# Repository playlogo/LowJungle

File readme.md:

# LowJungle

A low profile, ~65% keyboard, with:

- Hot swappable sockets
- Per key RGB backlight
- Wifi & BLE (but no battery)
- Integrated 3 port USB Hub

Links:

- [Onshape: Case](https://cad.onshape.com/documents/196ae99135554e28081e9cd8/w/09114671e2d692aadc408c6f/e/86be969bd7a114ceaf756b4a?renderMode=0&uiState=67d72bd2d4975832f10ffe5c)
- [Keyboard Layout Editor: Layout](https://www.keyboard-layout-editor.com/#/gists/81105ca4efea79bf3cdf03d682872e17)

## Firmware

For testing: KMK  
For production: QMK

> Circuitpython is soooo much nicer for finding errors in the hardware  
> Status KMK: Pins are correct, keymap is WIP

## PCB

- [Schematic](assets/schematic.pdf)
- No relevant ERC & DRC errors
- Size: 371.48mm x 133.35mm
- VCC for backlight LEDs can be controlled by the ESP32 using 2 mosfets
- Used libraries:
  - [Marbastlib, needs to be installed as plugin](https://github.com/ebastler/marbastlib/tree/main)
  - [easyeda2kicad, needs to be installed separately, used for downloading LCSC schematics & footprints](https://github.com/uPesy/easyeda2kicad.py)
    - Download `C2913204, C192893, C2891732, C778164, C2988369, C8547, C503996, C82942` using `easyeda2kicad --full --lcsc_id=<id>` (one-by-one, yes...)
  - `0_Custom`, included in the `libraries` folder, should load automatically

## Fabrication

> I'm print all parts myself using [the large scale 3D printer (Billig)](https://github.com/playlogo/billig) I'm build for [infill](https://github.com/hackclub/infill).

> Download the latest revision from [Onshape](https://cad.onshape.com/documents/196ae99135554e28081e9cd8/w/09114671e2d692aadc408c6f/e/86be969bd7a114ceaf756b4a?renderMode=0&uiState=67d72bd2d4975832f10ffe5c). STLs included with this repo are only meant as a backup if the onshape link ever stops working.

- Largest part: 380mmx145mm
- Recommended settings:
  - 6 wall loops
  - 6 solid top & bottom layers
  - 40% infill
- Notes:
  - `LowJungle-Backplate-V2.stl`: Should be solid
  - `LowJungle-Bumper-Bottom-V2.stl`: Print with TPU, 3x
  - `LowJungle-Bumper-Top-V2.stl`: 4x
  - `LowJungle-Frame-V2.stl`: Manually place tree supports for the USB connector cutouts

## BOM

**PCB:** [$36.34 at JLCPCB](assets/jlcpcb.png)

**Switches:** [Aliexpress: Gateron KS33 low-profile red, 90 for $38.63 => 0.43 per switch](https://de.aliexpress.com/item/1005007794069535.html)

**Keycaps:** [Aliexpress: Low profile set, 143 lily version, $21.61](https://de.aliexpress.com/item/1005004882406296.html)

**Stabilizers:** [Aliexpress: Gateron low-profile stabilizer set, 4x 2u 1x 6.25u, $13.79](https://de.aliexpress.com/item/1005005296240590.html)

**Fasteners:**

| Name | Price | Link |
|------|-------|------|
| 30x M2.5x3x3.5mm Heat insert | $1.83 | [Aliexpress](https://de.aliexpress.com/item/1005003582355741.html) |
| 14x M2.5x6mm Hex socket screw (for feet) | $1.41 | [Aliexpress](https://de.aliexpress.com/item/32810872544.html)|
| 16x M2.5x8mm Hex socket screw (for mounting frame) | $1.64 | [Aliexpress](https://de.aliexpress.com/item/32810872544.html) |
| 9x M3x10mm Hex socket screw | $1.79 | [Aliexpress](https://de.aliexpress.com/item/32810872544.html) |

Total: $6,67

**MCU:**

> Note: The ESP32S3 implementation is the same as in my [Hackpad](https://github.com/hackclub/hackpad/pull/570). Thus the cost can be drastically reduced when combining both LCSC orders:
>
> - -$3: Removed handling fee
> - -$6: Random shipping coupon
> - and often times the MOQ from hackpad also covers this project

|Name|Price|Link| Needed if combined order ? |
|----|-----|----|----------------------------|
|Espressif Systems ESP32-S3-WROOM-1-N8R2| $4.41| [LCSC](https://www.lcsc.com/product-detail/WiFi-Modules_Espressif-Systems-ESP32-S3-WROOM-1-N8R2_C2913204.html)| Yes|
| N-Channel mosfet | $0.6 for MOQ | [LCSC](https://www.lcsc.com/product-detail/MOSFETs_YONGYUTAI-SI2302_C2891732.html)| Yes |
|3.3V LDO | $0.48 for MOQ| [LCSC](https://www.lcsc.com/product-detail/Voltage-Regulators-Linear-Low-Drop-Out-LDO-Regulators_MICRONE-Nanjing-Micro-One-Elec-ME6211C33M5G-N_C82942.html?s_z=n_ME6211C33M5G-N)| No |
| USB-A female| $0.42 for MOQ | [LCSC](https://www.lcsc.com/product-detail/USB-Connectors_Shenzhen-Kinghelm-Elec-KH-AF90DIP-112_C503996.html?s_z=n_usb%20a)|No |
| USB-C female| $0.4 for MOQ | [LCSC](https://www.lcsc.com/product-detail/USB-Connectors_G-Switch-GT-USB-7010ASV_C2988369.html?s_z=n_G-Switch%20GT-USB-7010asv)|No |
| P-Channel mosfet | $0.49 for MOQ | [LCSC](https://www.lcsc.com/product-detail/MOSFETs_Jiangsu-Changjing-Electronics-Technology-Co-Ltd-CJ2301-S1_C8547.html)|No |
| Mini push button | $0.47 for MOQ | [LCSC](https://www.lcsc.com/product-detail/Tactile-Switches_G-Switch-GT-TC029A-H020-L1N_C778164.html?s_z=n_SKRKAEE020)|No |
| CoreChips SL2.1A USB Hub driver | $1.32 for MOQ | [LCSC](https://www.lcsc.com/product-detail/USB-HUB-Controllers_CoreChips-SL2-1A_C192893.html?s_z=n_C192893)|No |
|---|----|---|---|
| 1N4148 Diodes | $1.04 for 100 | [LCSC](https://www.lcsc.com/product-detail/Switching-Diodes_LangJie-1N4148_C18195411.html?s_z=n_1N4148%2520Diodes) | Yes |
|10uF 0805 Capacitor | $0.16 for MOQ| [LCSC](https://www.lcsc.com/product-detail/Multilayer-Ceramic-Capacitors-MLCC-SMD-SMT_Samsung-Electro-Mechanics-CL21A106KOQNNNE_C1713.html)| No|
| 100nF * | $0.3 for MOQ | [LCSC](https://www.lcsc.com/product-detail/Multilayer-Ceramic-Capacitors-MLCC-SMD-SMT_FH-Guangdong-Fenghua-Advanced-Tech-0805B104J500NT_C29926.html)|No|
| 1uF * | $1 for MOQ | [LCSC](https://www.lcsc.com/product-detail/Multilayer-Ceramic-Capacitors-MLCC-SMD-SMT_YAGEO-CC0805JKX7R9BB105_C541528.html) | No |
|10k 0805 Resistor | $0.13 for MOQ | [LCSC](https://www.lcsc.com/product-detail/Chip-Resistor-Surface-Mount_VO-SCR0805J10K_C5140188.html?s_z=n_resistor)| No|
| 5.1k * | $0.15 for MOQ | [LCSC](https://www.lcsc.com/product-detail/Chip-Resistor-Surface-Mount_UNI-ROYAL-Uniroyal-Elec-0805W8J0512T5E_C26023.html?s_z=n_resistor) | No |
| 100k * |  $0.13 for MOQ | [LCSC](https://www.lcsc.com/product-detail/Chip-Resistor-Surface-Mount_VO-SCR0805J100K_C3017875.html?s_z=n_resistor) | No |

Total (without combined order): $11.46  
Total (with combined order): $6.01

>Note: Combined LCSC order will be around ~$28 (including shipping) for both hackpad and hackboard

**Misc Electronics:**

|Name|Price|Link|
| ----- | ---- | ---- |
| SK6812 MINI-E | $2.85 for 100 | [Aliexpress](https://de.aliexpress.com/item/1005002782417198.html) |
| Gateron Low-profile hot-swap socket | $9.03 for 100 => $0.1 per socket | [Aliexpress](https://de.aliexpress.com/item/1005008078611488.html?spm=a2g0o.productlist.main.1.3d3470f0o9Li2s&algo_pvid=ef243bac-f923-4f5b-85e0-b6818cdc378c&pdp_ext_f=%7B%22order%22%3A%2223%22%2C%22eval%22%3A%221%22%7D&utparam-url=scene%3Asearch%7Cquery_from%3A) |
| Rotary-encoder | in stock | - |

Total: $11.88

**Other parts:**

|Name|Reason|Price|Link|
|----|------|-----|----|
| Poron foam, Bottom case <-> PCB, 2.5mm 15x35cm | Sound damping | $6.10 | [Aliexpress](https://de.aliexpress.com/item/1005007442653383.html)|
| EVA foam, PCB <-> Top plate , 1mm 35x50cm | Stability of top plate |  $2.05 | [Aliexpress](https://de.aliexpress.com/item/1005002856054113.html)|
|EVA foam, PCB <-> Keyswitch  | Sound damping | $3.42 | [Aliexpress](https://de.aliexpress.com/item/1005005556269716.html)|
|PE foam, Top plate <-> Keyswitch | Water spill protection (has happened before) | $2.19 | [Aliexpress](https://de.aliexpress.com/item/1005004804230184.html)|

Total: $13,76

### BOM total

**Fasteners:** $6,67
**PCB:** $36.34  
**Switches:** $38.63  
**Keycaps:** $21.61  
**Stabilizers:** $13.79  
**MCU:** $6.01  
**Misc Electronics:** $11.88  
**Other parts:** $13,76

**Total:** $148,69

> Note: Aliexpress prices are only valid until 26. March (15. anniversary sale)
> => If the grant is issued after 24. March, it would be awesome to have ~$15 buffer for changed prices. The unused amount would be returned to HackClub.

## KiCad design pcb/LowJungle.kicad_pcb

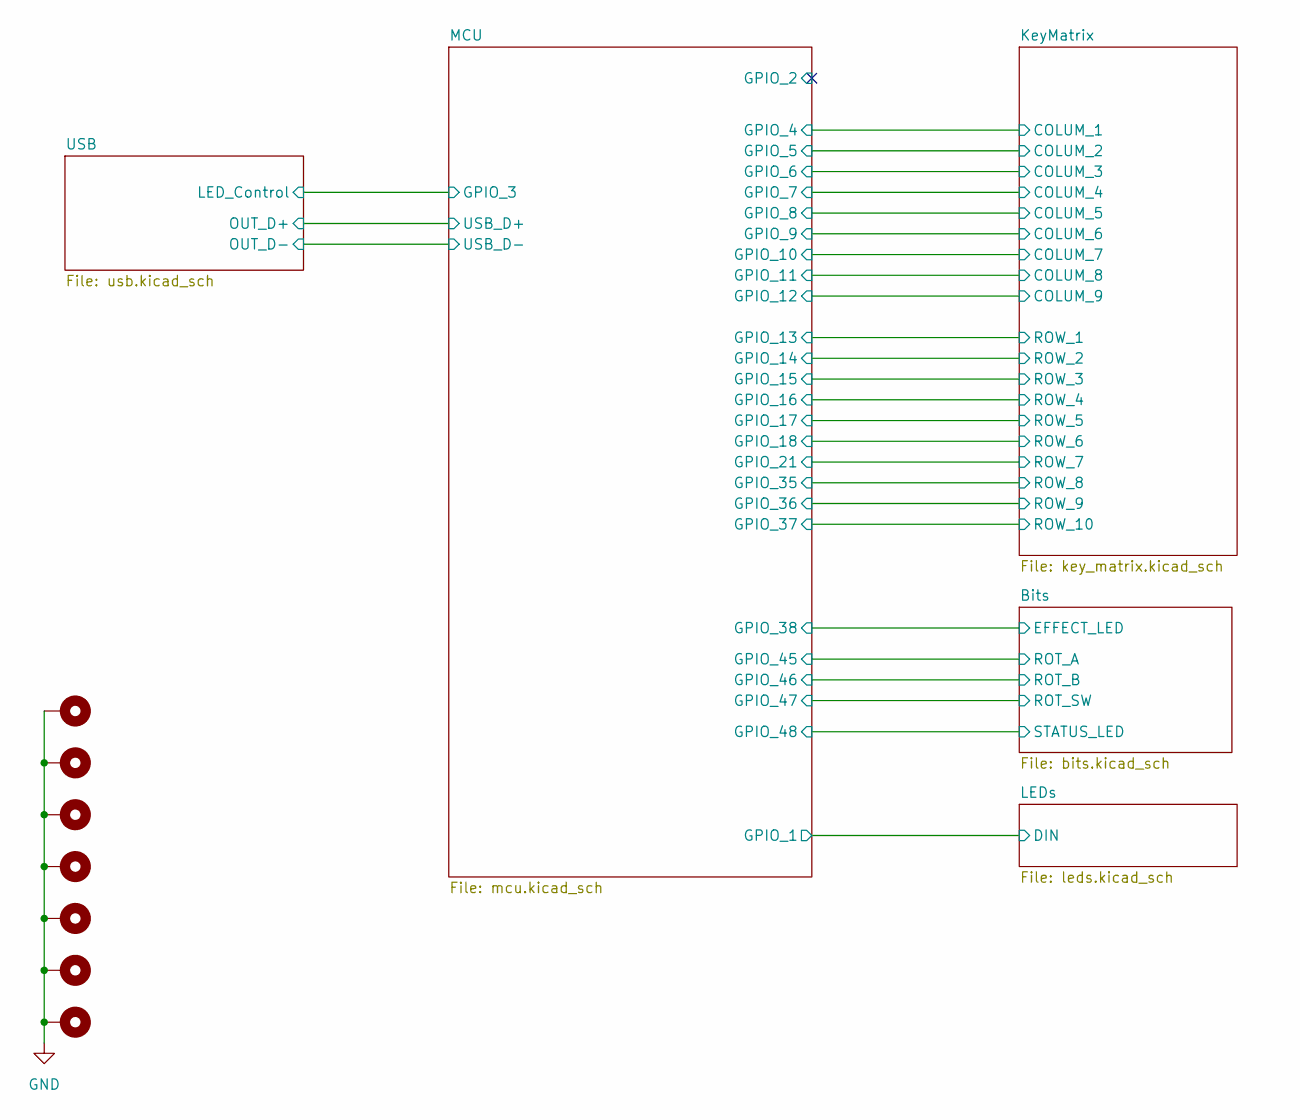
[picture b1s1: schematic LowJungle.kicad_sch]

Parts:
H1, H2, H3, H4, H5, H6, H7: MountingHole_Pad; MountingHole_3.2mm_M3_DIN965_Pad_TopOnly

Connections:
GND: H1.1, H2.1, H3.1, H4.1, H5.1, H6.1, H7.1; also elsewhere on the board

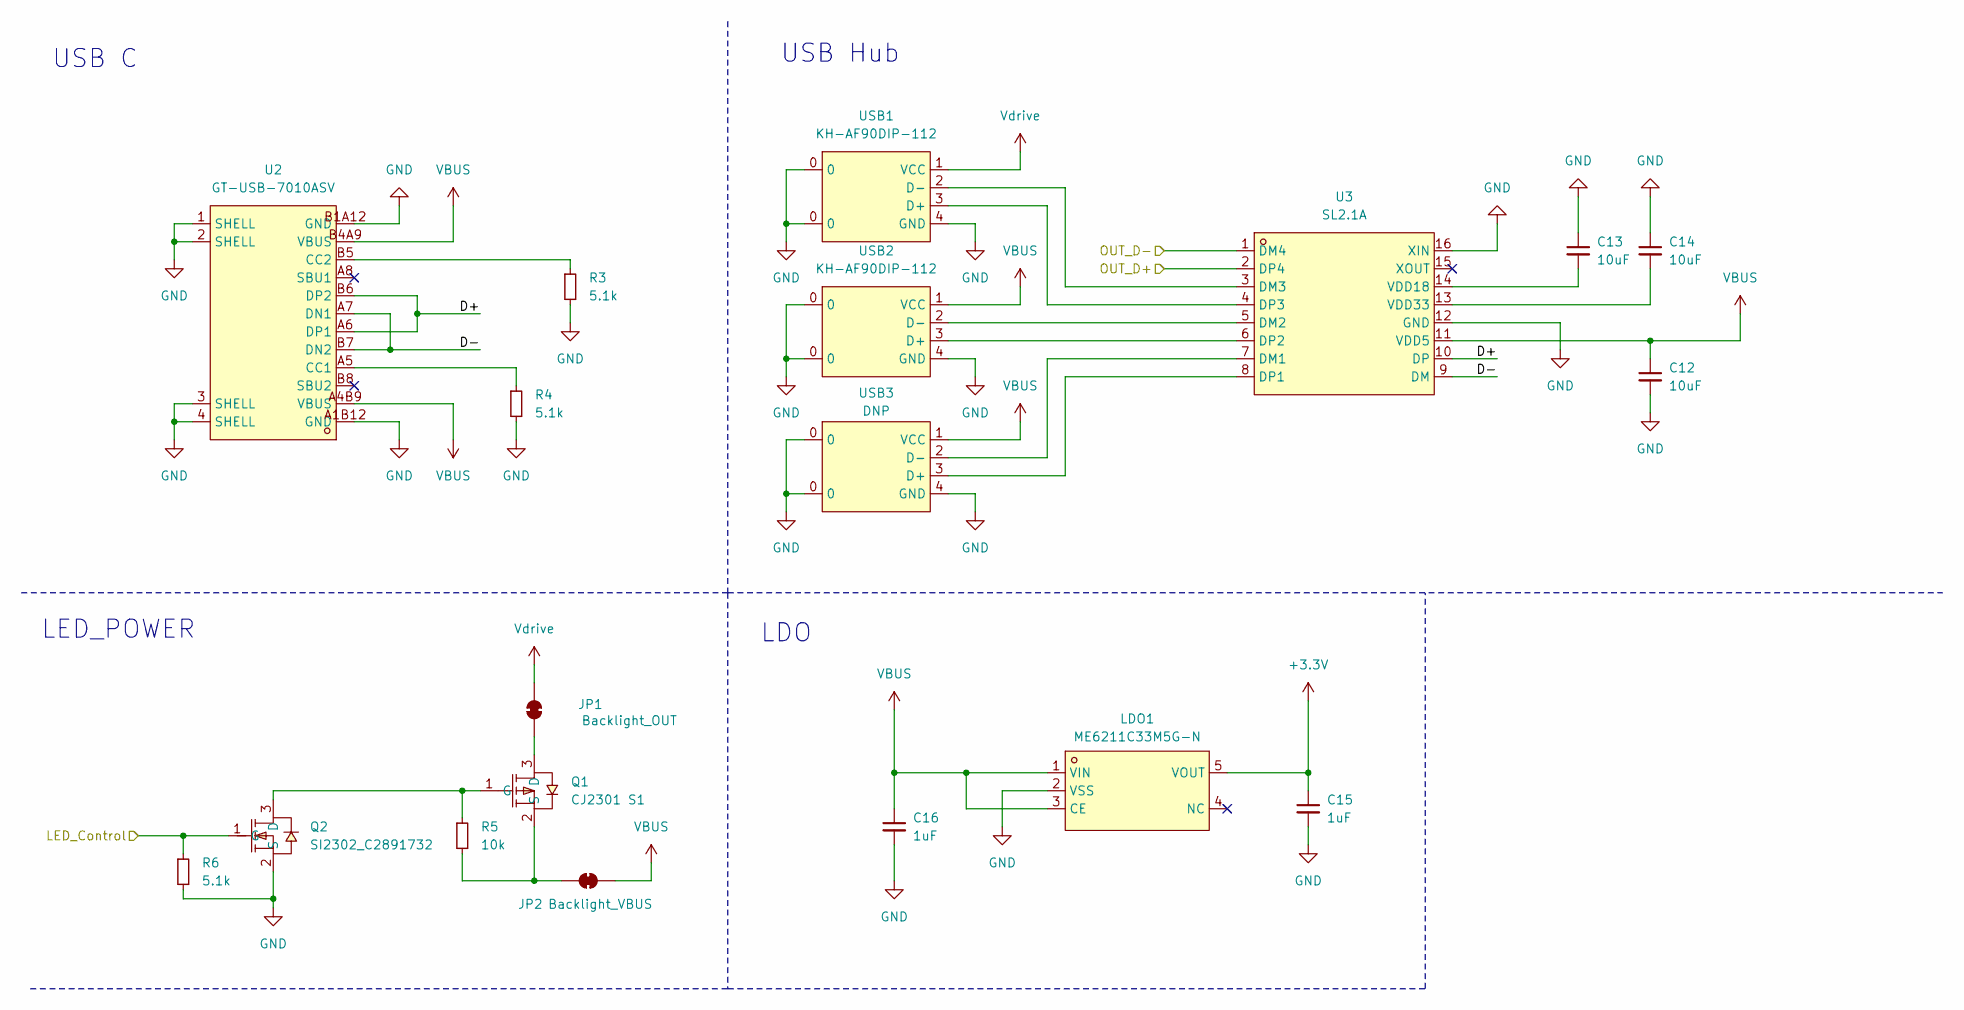
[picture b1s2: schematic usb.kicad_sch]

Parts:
C12, C13, C14: 10uF; C_0805_2012Metric_Pad1.18x1.45mm_HandSolder
C15, C16: 1uF; C_0805_2012Metric_Pad1.18x1.45mm_HandSolder
JP1: Backlight_OUT; SolderJumper-2_P1.3mm_Bridged2Bar_RoundedPad1.0x1.5mm
JP2: Backlight_VBUS; SolderJumper-2_P1.3mm_Bridged2Bar_RoundedPad1.0x1.5mm
LDO1: ME6211C33M5G-N; SOT-23-5_L3.0-W1.7-P0.95-LS2.8-BL; LCSC Part C82942
Q1: CJ2301 S1; SOT-23-3_L3.0-W1.7-P0.95-LS2.9-BR; LCSC Part C8547
Q2: SI2302_C2891732; SOT-23-3_L2.9-W1.3-P1.90-LS2.4-BR; LCSC Part C2891732
R3, R4, R6: 5.1k; R_0805_2012Metric_Pad1.20x1.40mm_HandSolder
R5: 10k; R_0805_2012Metric_Pad1.20x1.40mm_HandSolder
U2: GT-USB-7010ASV; USB-C-SMD_G-SWITCH_GT-USB-7010ASV; LCSC Part C2988369
U3: SL2.1A; SOP-16_L10.0-W3.9-P1.27-LS6.0-BL; LCSC Part C192893
USB1, USB2: KH-AF90DIP-112; USB-A-TH_USB-A-F-90; LCSC Part C503996
USB3: DNP; USB-A-TH_USB-A-F-90; LCSC Part C503996

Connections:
+3.3V: C15.1, LDO1.5 (VOUT); also elsewhere on the board
/MCU/GPIO_3: Q2.1 (G), R6.1; also elsewhere on the board
/MCU/USB_D+: U3.2 (DP4); also elsewhere on the board
/MCU/USB_D-: U3.1 (DM4); also elsewhere on the board
/USB/D+: U2.A6 (DP1), U2.B6 (DP2), U3.10 (DP)
/USB/D-: U2.A7 (DN1), U2.B7 (DN2), U3.9 (DM)
GND: C12.2, C13.1, C14.1, C15.2, C16.2, LDO1.2 (VSS), Q2.2 (S), R3.2, R4.2, R6.2, U2.1 (SHELL), U2.2 (SHELL), U2.3 (SHELL), U2.4 (SHELL), U2.A1B12 (GND), U2.B1A12 (GND), U3.12 (GND), U3.16 (XIN), USB1.0, USB1.4 (GND), USB2.0, USB2.4 (GND), USB3.0, USB3.4 (GND); also elsewhere on the board
unnamed: JP1.1 (A), Q1.3 (D)
unnamed: JP2.1 (A), Q1.2 (S), R5.2
unnamed: Q1.1 (G), Q2.3 (D), R5.1
unnamed: R4.1, U2.A5 (CC1)
unnamed: R3.1, U2.B5 (CC2)
unnamed: U3.7 (DM1), USB3.2 (D-)
unnamed: U3.5 (DM2), USB2.2 (D-)
unnamed: U3.3 (DM3), USB1.2 (D-)
unnamed: U3.8 (DP1), USB3.3 (D+)
unnamed: U3.6 (DP2), USB2.3 (D+)
unnamed: U3.4 (DP3), USB1.3 (D+)
unnamed: C13.2, U3.14 (VDD18)
unnamed: C14.2, U3.13 (VDD33)
VBUS: C12.1, C16.1, JP2.2 (B), LDO1.1 (VIN), LDO1.3 (CE), U2.A4B9 (VBUS), U2.B4A9 (VBUS), U3.11 (VDD5), USB2.1 (VCC), USB3.1 (VCC); also elsewhere on the board
Vdrive: JP1.2 (B), USB1.1 (VCC); also elsewhere on the board

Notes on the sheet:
USB Hub
LED_POWER
USB C
LDO

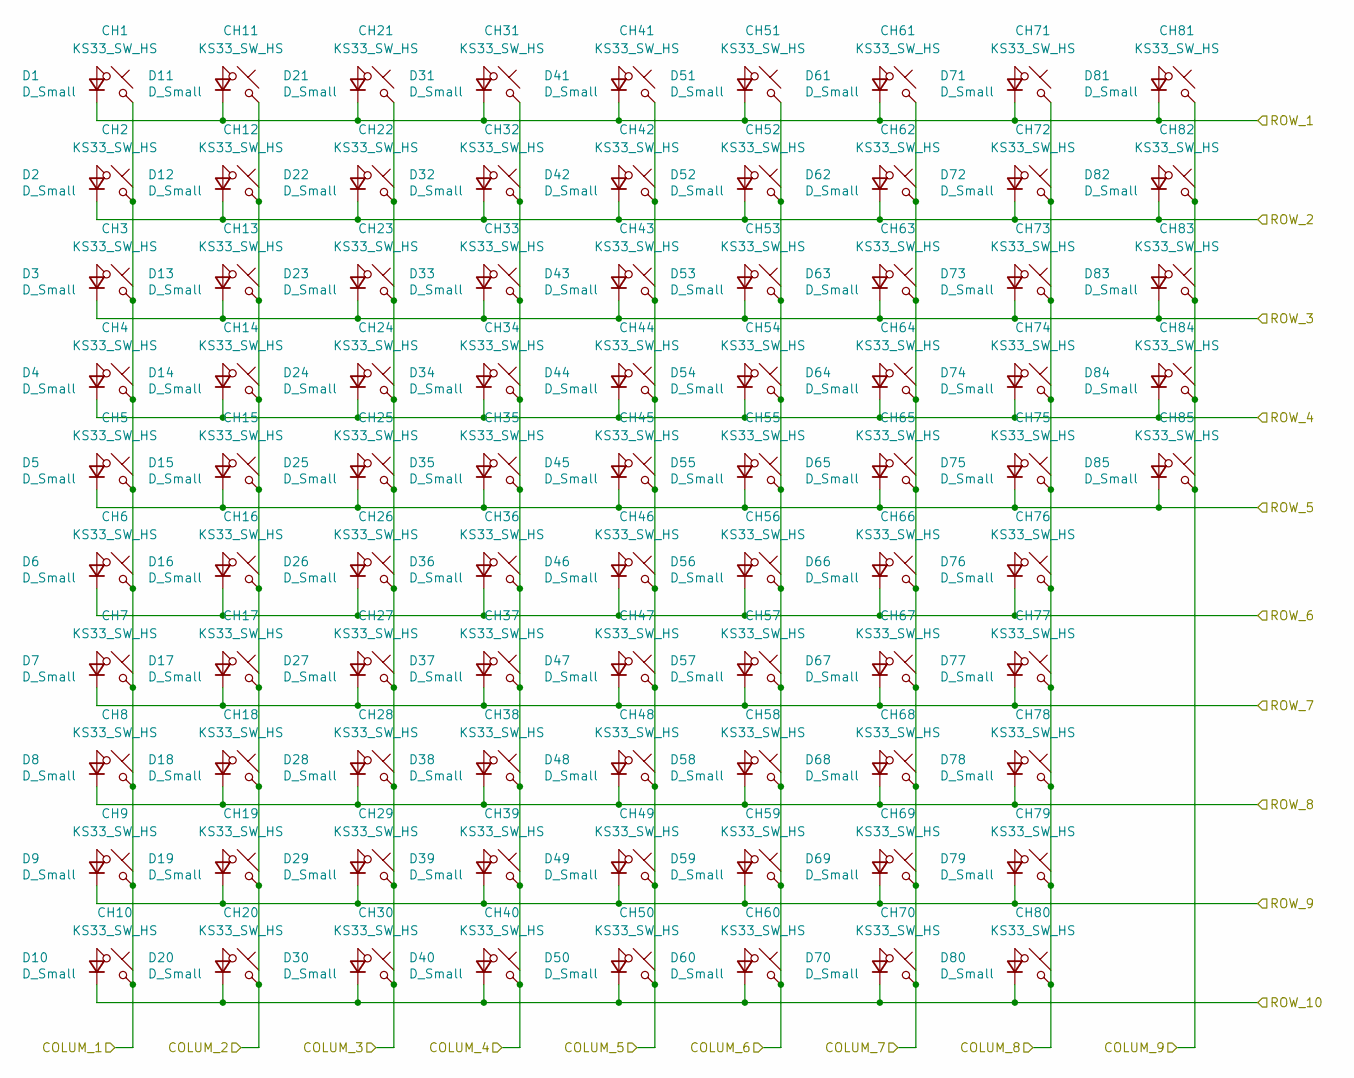
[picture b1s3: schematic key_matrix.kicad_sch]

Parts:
CH1, CH2, CH7, CH8, CH9, CH10, CH12, CH13, CH14, CH15, CH16, CH18, CH19, CH20, CH21, CH22, CH23, CH24, CH25, CH26, CH27, CH28, CH29, CH30, CH31, CH32, CH33, CH34, CH35, CH36, CH37, CH38, CH39, CH40, CH41, CH42, CH43, CH44, CH45, CH46, CH47, CH48, CH49, CH50, CH51, CH52, CH53, CH54, CH55, CH56, CH57, CH58, CH59, CH60, CH61, CH62, CH63, CH64, CH65, CH67, CH70, CH74, CH75, CH76, CH77, CH78, CH79, CH80, CH81, CH82, CH83, CH84, CH85: KS33_SW_HS; SW_KS33_HS_KS-2P02B01-02_HS_1u
CH3, CH68: KS33_SW_HS; SW_KS33_HS_KS-2P02B01-02_1.5u
CH4: KS33_SW_HS; SW_KS33_HS_KS-2P02B01-02_1.75u
CH5, CH6, CH11, CH17, CH66, CH69, CH71, CH72, CH73: KS33_SW_HS; SW_KS33_HS_KS-2P02B01-02_1.25u
D1, D2, D3, D4, D5, D6, D7, D8, D9, D10, D11, D12, D13, D14, D15, D16, D17, D18, D19, D20, D21, D22, D23, D24, D25, D26, D27, D28, D29, D30, D31, D32, D33, D34, D35, D36, D37, D38, D39, D40, D41, D42, D43, D44, D45, D46, D47, D48, D49, D50, D51, D52, D53, D54, D55, D56, D57, D58, D59, D60, D61, D62, D63, D64, D65, D66, D67, D68, D69, D70, D71, D72, D73, D74, D75, D76, D77, D78, D79, D80, D81, D82, D83, D84, D85: D_Small; D_DO-35_SOD27_P7.62mm_Horizontal

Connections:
/KeyMatrix/COLUM_1: CH1.2, CH2.2, CH3.2, CH4.2, CH5.2, CH6.2, CH7.2, CH8.2, CH9.2, CH10.2; also elsewhere on the board
/KeyMatrix/COLUM_2: CH11.2, CH12.2, CH13.2, CH14.2, CH15.2, CH16.2, CH17.2, CH18.2, CH19.2, CH20.2; also elsewhere on the board
/KeyMatrix/COLUM_3: CH21.2, CH22.2, CH23.2, CH24.2, CH25.2, CH26.2, CH27.2, CH28.2, CH29.2, CH30.2; also elsewhere on the board
/KeyMatrix/COLUM_4: CH31.2, CH32.2, CH33.2, CH34.2, CH35.2, CH36.2, CH37.2, CH38.2, CH39.2, CH40.2; also elsewhere on the board
/KeyMatrix/COLUM_5: CH41.2, CH42.2, CH43.2, CH44.2, CH45.2, CH46.2, CH47.2, CH48.2, CH49.2, CH50.2; also elsewhere on the board
/KeyMatrix/COLUM_6: CH51.2, CH52.2, CH53.2, CH54.2, CH55.2, CH56.2, CH57.2, CH58.2, CH59.2, CH60.2; also elsewhere on the board
/KeyMatrix/COLUM_7: CH61.2, CH62.2, CH63.2, CH64.2, CH65.2, CH66.2, CH67.2, CH68.2, CH69.2, CH70.2; also elsewhere on the board
/KeyMatrix/COLUM_8: CH71.2, CH72.2, CH73.2, CH74.2, CH75.2, CH76.2, CH77.2, CH78.2, CH79.2, CH80.2; also elsewhere on the board
/KeyMatrix/COLUM_9: CH81.2, CH82.2, CH83.2, CH84.2, CH85.2; also elsewhere on the board
/KeyMatrix/ROW_1: D1.1 (K), D11.1 (K), D21.1 (K), D31.1 (K), D41.1 (K), D51.1 (K), D61.1 (K), D71.1 (K), D81.1 (K); also elsewhere on the board
/KeyMatrix/ROW_2: D2.1 (K), D12.1 (K), D22.1 (K), D32.1 (K), D42.1 (K), D52.1 (K), D62.1 (K), D72.1 (K), D82.1 (K); also elsewhere on the board
/KeyMatrix/ROW_3: D3.1 (K), D13.1 (K), D23.1 (K), D33.1 (K), D43.1 (K), D53.1 (K), D63.1 (K), D73.1 (K), D83.1 (K); also elsewhere on the board
/KeyMatrix/ROW_4: D4.1 (K), D14.1 (K), D24.1 (K), D34.1 (K), D44.1 (K), D54.1 (K), D64.1 (K), D74.1 (K), D84.1 (K); also elsewhere on the board
/KeyMatrix/ROW_5: D5.1 (K), D15.1 (K), D25.1 (K), D35.1 (K), D45.1 (K), D55.1 (K), D65.1 (K), D75.1 (K), D85.1 (K); also elsewhere on the board
/KeyMatrix/ROW_6: D6.1 (K), D16.1 (K), D26.1 (K), D36.1 (K), D46.1 (K), D56.1 (K), D66.1 (K), D76.1 (K); also elsewhere on the board
/KeyMatrix/ROW_7: D7.1 (K), D17.1 (K), D27.1 (K), D37.1 (K), D47.1 (K), D57.1 (K), D67.1 (K), D77.1 (K); also elsewhere on the board
/KeyMatrix/ROW_8: D8.1 (K), D18.1 (K), D28.1 (K), D38.1 (K), D48.1 (K), D58.1 (K), D68.1 (K), D78.1 (K); also elsewhere on the board
/KeyMatrix/ROW_9: D9.1 (K), D19.1 (K), D29.1 (K), D39.1 (K), D49.1 (K), D59.1 (K), D69.1 (K), D79.1 (K); also elsewhere on the board
/KeyMatrix/ROW_10: D10.1 (K), D20.1 (K), D30.1 (K), D40.1 (K), D50.1 (K), D60.1 (K), D70.1 (K), D80.1 (K); also elsewhere on the board
unnamed: CH1.1, D1.2 (A)
unnamed: CH2.1, D2.2 (A)
unnamed: CH3.1, D3.2 (A)
unnamed: CH4.1, D4.2 (A)
unnamed: CH5.1, D5.2 (A)
unnamed: CH6.1, D6.2 (A)
unnamed: CH7.1, D7.2 (A)
unnamed: CH8.1, D8.2 (A)
unnamed: CH9.1, D9.2 (A)
unnamed: CH10.1, D10.2 (A)
unnamed: CH11.1, D11.2 (A)
unnamed: CH12.1, D12.2 (A)
unnamed: CH13.1, D13.2 (A)
unnamed: CH14.1, D14.2 (A)
unnamed: CH15.1, D15.2 (A)
unnamed: CH16.1, D16.2 (A)
unnamed: CH17.1, D17.2 (A)
unnamed: CH18.1, D18.2 (A)
unnamed: CH19.1, D19.2 (A)
unnamed: CH20.1, D20.2 (A)
unnamed: CH21.1, D21.2 (A)
unnamed: CH22.1, D22.2 (A)
unnamed: CH23.1, D23.2 (A)
unnamed: CH24.1, D24.2 (A)
unnamed: CH25.1, D25.2 (A)
unnamed: CH26.1, D26.2 (A)
unnamed: CH27.1, D27.2 (A)
unnamed: CH28.1, D28.2 (A)
unnamed: CH29.1, D29.2 (A)
unnamed: CH30.1, D30.2 (A)
unnamed: CH31.1, D31.2 (A)
unnamed: CH32.1, D32.2 (A)
unnamed: CH33.1, D33.2 (A)
unnamed: CH34.1, D34.2 (A)
unnamed: CH35.1, D35.2 (A)
unnamed: CH36.1, D36.2 (A)
unnamed: CH37.1, D37.2 (A)
unnamed: CH38.1, D38.2 (A)
unnamed: CH39.1, D39.2 (A)
unnamed: CH40.1, D40.2 (A)
unnamed: CH41.1, D41.2 (A)
unnamed: CH42.1, D42.2 (A)
unnamed: CH43.1, D43.2 (A)
unnamed: CH44.1, D44.2 (A)
unnamed: CH45.1, D45.2 (A)
unnamed: CH46.1, D46.2 (A)
unnamed: CH47.1, D47.2 (A)
unnamed: CH48.1, D48.2 (A)
unnamed: CH49.1, D49.2 (A)
unnamed: CH50.1, D50.2 (A)
unnamed: CH51.1, D51.2 (A)
unnamed: CH52.1, D52.2 (A)
unnamed: CH53.1, D53.2 (A)
unnamed: CH54.1, D54.2 (A)
unnamed: CH55.1, D55.2 (A)
unnamed: CH56.1, D56.2 (A)
unnamed: CH57.1, D57.2 (A)
unnamed: CH58.1, D58.2 (A)
unnamed: CH59.1, D59.2 (A)
unnamed: CH60.1, D60.2 (A)
unnamed: CH61.1, D61.2 (A)
unnamed: CH62.1, D62.2 (A)
unnamed: CH63.1, D63.2 (A)
unnamed: CH64.1, D64.2 (A)
unnamed: CH65.1, D65.2 (A)
unnamed: CH66.1, D66.2 (A)
unnamed: CH67.1, D67.2 (A)
unnamed: CH68.1, D68.2 (A)
unnamed: CH69.1, D69.2 (A)
unnamed: CH70.1, D70.2 (A)
unnamed: CH71.1, D71.2 (A)
unnamed: CH72.1, D72.2 (A)
unnamed: CH73.1, D73.2 (A)
unnamed: CH74.1, D74.2 (A)
unnamed: CH75.1, D75.2 (A)
unnamed: CH76.1, D76.2 (A)
unnamed: CH77.1, D77.2 (A)
unnamed: CH78.1, D78.2 (A)
unnamed: CH79.1, D79.2 (A)
unnamed: CH80.1, D80.2 (A)
unnamed: CH81.1, D81.2 (A)
unnamed: CH82.1, D82.2 (A)
unnamed: CH83.1, D83.2 (A)
unnamed: CH84.1, D84.2 (A)
unnamed: CH85.1, D85.2 (A)

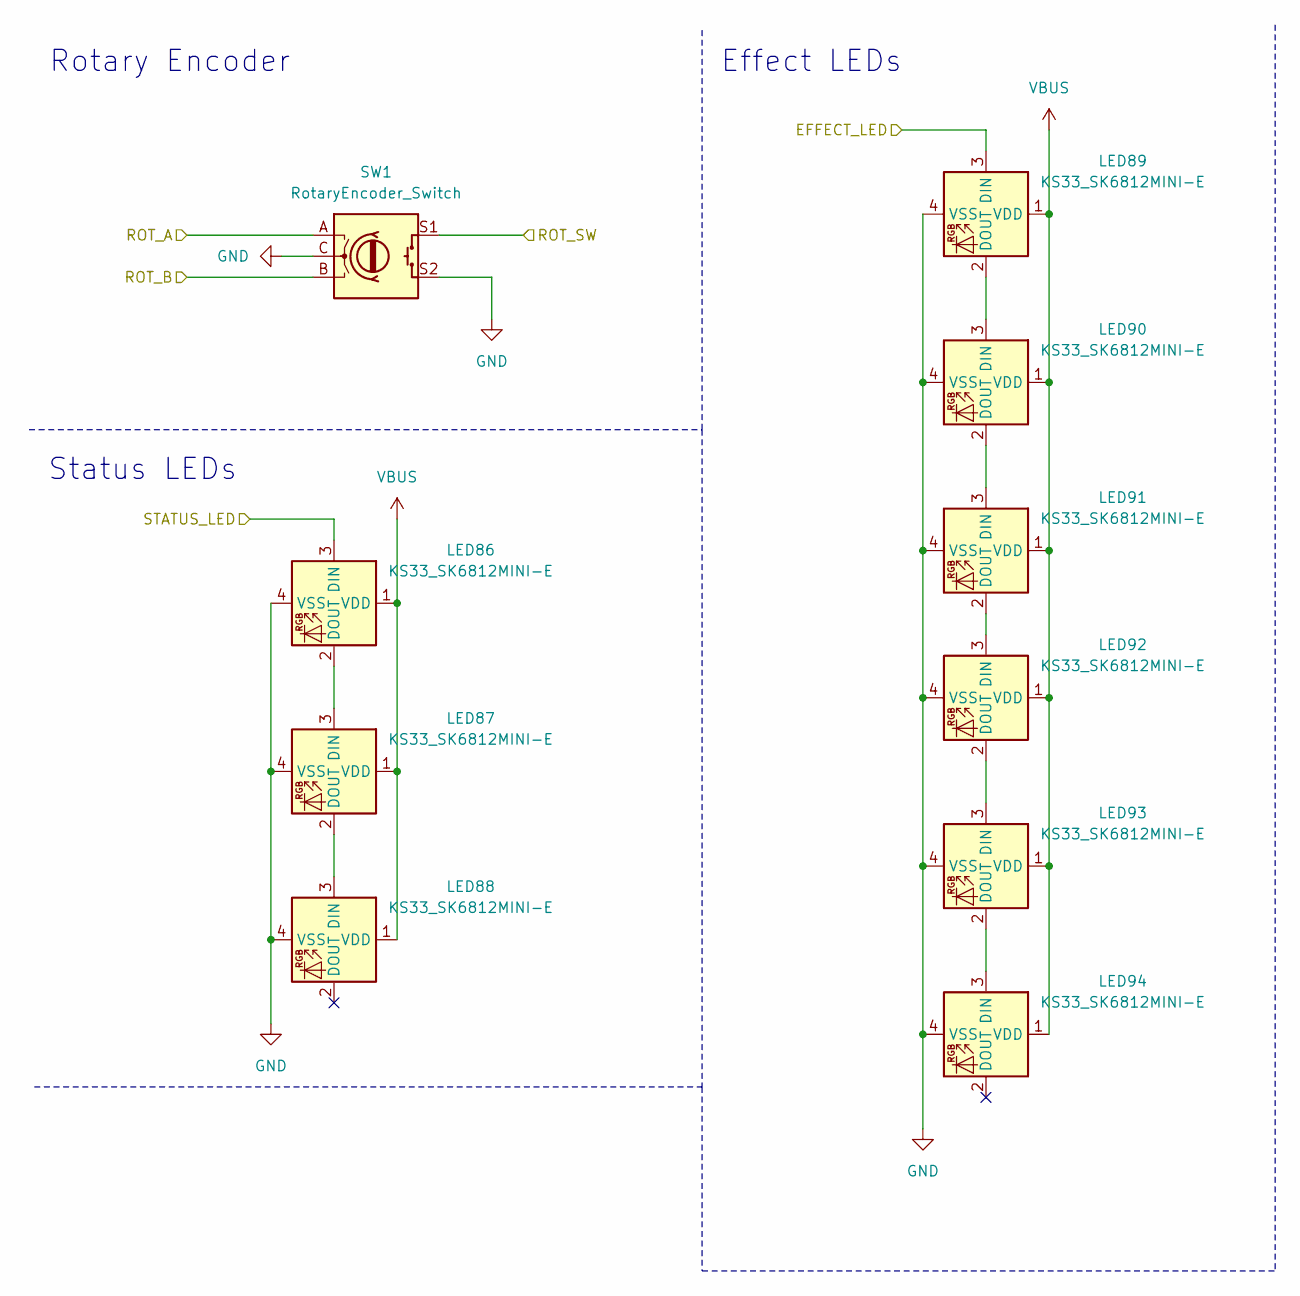
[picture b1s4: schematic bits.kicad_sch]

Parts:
LED86, LED87, LED88, LED89, LED90, LED91, LED92, LED93, LED94: KS33_SK6812MINI-E; LED_KS33_6028R
SW1: RotaryEncoder_Switch; RotaryEncoder_Alps_EC11E-Switch_Vertical_H20mm_CircularMoun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

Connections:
/Bits/EFFECT_LED: LED89.3 (DIN); also elsewhere on the board
/Bits/ROT_A: SW1.A; also elsewhere on the board
/Bits/ROT_B: SW1.B; also elsewhere on the board
/Bits/ROT_SW: SW1.S1; also elsewhere on the board
/Bits/STATUS_LED: LED86.3 (DIN); also elsewhere on the board
GND: LED86.4 (VSS), LED87.4 (VSS), LED88.4 (VSS), LED89.4 (VSS), LED90.4 (VSS), LED91.4 (VSS), LED92.4 (VSS), LED93.4 (VSS), LED94.4 (VSS), SW1.C, SW1.S2; also elsewhere on the board
unnamed: LED86.2 (DOUT), LED87.3 (DIN)
unnamed: LED87.2 (DOUT), LED88.3 (DIN)
unnamed: LED89.2 (DOUT), LED90.3 (DIN)
unnamed: LED90.2 (DOUT), LED91.3 (DIN)
unnamed: LED91.2 (DOUT), LED92.3 (DIN)
unnamed: LED92.2 (DOUT), LED93.3 (DIN)
unnamed: LED93.2 (DOUT), LED94.3 (DIN)
VBUS: LED86.1 (VDD), LED87.1 (VDD), LED88.1 (VDD), LED89.1 (VDD), LED90.1 (VDD), LED91.1 (VDD), LED92.1 (VDD), LED93.1 (VDD), LED94.1 (VDD); also elsewhere on the board

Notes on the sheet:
Status LEDs
Effect LEDs
Rotary Encoder

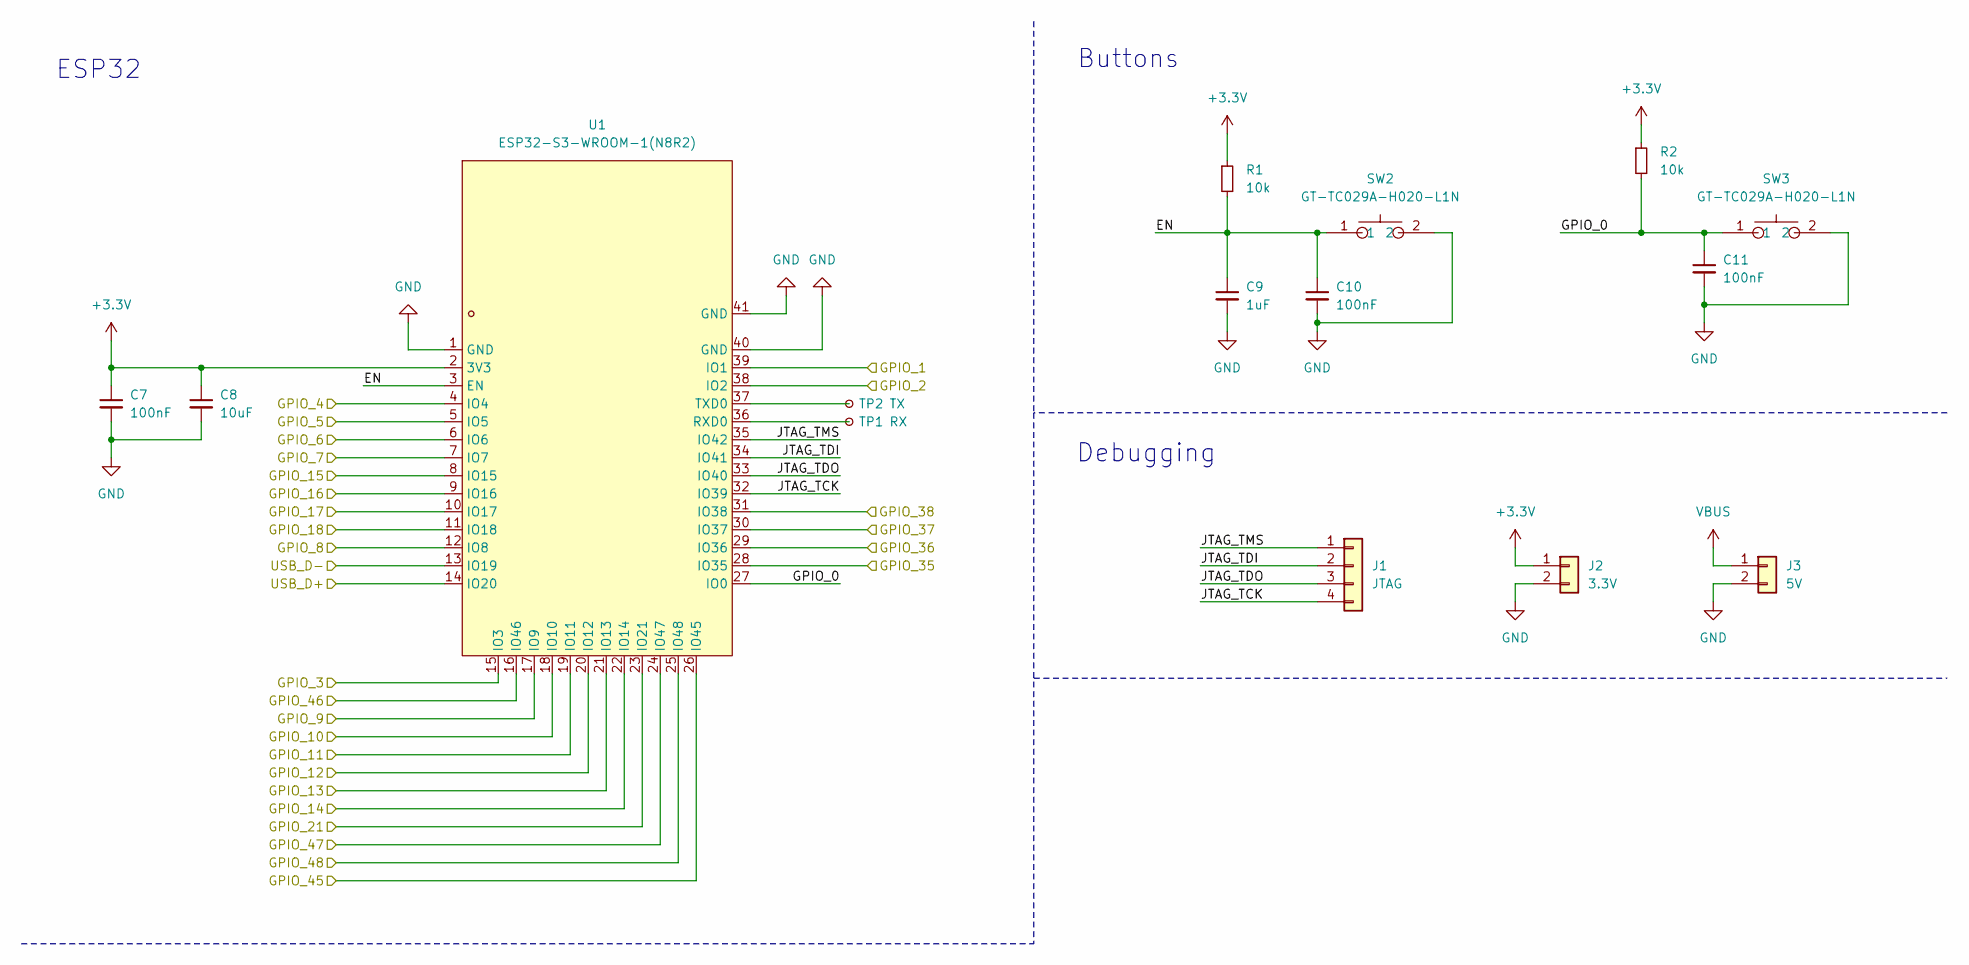
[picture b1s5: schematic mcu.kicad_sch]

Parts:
C7, C10, C11: 100nF; C_0805_2012Metric_Pad1.18x1.45mm_HandSolder
C8: 10uF; C_0805_2012Metric_Pad1.18x1.45mm_HandSolder
C9: 1uF; C_0805_2012Metric_Pad1.18x1.45mm_HandSolder
J1: JTAG; PinHeader_1x04_P1.00mm_Vertical
J2: 3.3V; PinHeader_1x02_P1.00mm_Vertical
J3: 5V; PinHeader_1x02_P1.00mm_Vertical
R1, R2: 10k; R_0805_2012Metric_Pad1.20x1.40mm_HandSolder
SW2, SW3: GT-TC029A-H020-L1N; SW-SMD_L3.9-W2.9-LS5.0; LCSC Part C778164
TP1: RX; TestPoint_Pad_D1.0mm
TP2: TX; TestPoint_Pad_D1.0mm
U1: ESP32-S3-WROOM-1(N8R2); WIRELM-SMD_ESP32-S3-WROOM-1; LCSC Part C2913204

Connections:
+3.3V: C7.1, C8.1, J2.1, R1.1, R2.1, U1.2 (3V3); also elsewhere on the board
/Bits/EFFECT_LED: U1.31 (IO38); also elsewhere on the board
/Bits/ROT_A: U1.26 (IO45); also elsewhere on the board
/Bits/ROT_B: U1.16 (IO46); also elsewhere on the board
/Bits/ROT_SW: U1.24 (IO47); also elsewhere on the board
/Bits/STATUS_LED: U1.25 (IO48); also elsewhere on the board
/KeyMatrix/COLUM_1: U1.4 (IO4); also elsewhere on the board
/KeyMatrix/COLUM_2: U1.5 (IO5); also elsewhere on the board
/KeyMatrix/COLUM_3: U1.6 (IO6); also elsewhere on the board
/KeyMatrix/COLUM_4: U1.7 (IO7); also elsewhere on the board
/KeyMatrix/COLUM_5: U1.12 (IO8); also elsewhere on the board
/KeyMatrix/COLUM_6: U1.17 (IO9); also elsewhere on the board
/KeyMatrix/COLUM_7: U1.18 (IO10); also elsewhere on the board
/KeyMatrix/COLUM_8: U1.19 (IO11); also elsewhere on the board
/KeyMatrix/COLUM_9: U1.20 (IO12); also elsewhere on the board
/KeyMatrix/ROW_1: U1.21 (IO13); also elsewhere on the board
/KeyMatrix/ROW_2: U1.22 (IO14); also elsewhere on the board
/KeyMatrix/ROW_3: U1.8 (IO15); also elsewhere on the board
/KeyMatrix/ROW_4: U1.9 (IO16); also elsewhere on the board
/KeyMatrix/ROW_5: U1.10 (IO17); also elsewhere on the board
/KeyMatrix/ROW_6: U1.11 (IO18); also elsewhere on the board
/KeyMatrix/ROW_7: U1.23 (IO21); also elsewhere on the board
/KeyMatrix/ROW_8: U1.28 (IO35); also elsewhere on the board
/KeyMatrix/ROW_9: U1.29 (IO36); also elsewhere on the board
/KeyMatrix/ROW_10: U1.30 (IO37); also elsewhere on the board
/LEDs/DIN: U1.39 (IO1); also elsewhere on the board
/MCU/EN: C9.1, C10.1, R1.2, SW2.1, U1.3 (EN)
/MCU/GPIO_0: C11.1, R2.2, SW3.1, U1.27 (IO0)
/MCU/GPIO_2: U1.38 (IO2)
/MCU/GPIO_3: U1.15 (IO3); also elsewhere on the board
/MCU/JTAG_TCK: J1.4, U1.32 (IO39)
/MCU/JTAG_TDI: J1.2, U1.34 (IO41)
/MCU/JTAG_TDO: J1.3, U1.33 (IO40)
/MCU/JTAG_TMS: J1.1, U1.35 (IO42)
/MCU/USB_D+: U1.14 (IO20); also elsewhere on the board
/MCU/USB_D-: U1.13 (IO19); also elsewhere on the board
GND: C7.2, C8.2, C9.2, C10.2, C11.2, J2.2, J3.2, SW2.2, SW3.2, U1.1 (GND), U1.40 (GND), U1.41 (GND); also elsewhere on the board
unnamed: TP1.1, U1.36 (RXD0)
unnamed: TP2.1, U1.37 (TXD0)
VBUS: J3.1; also elsewhere on the board

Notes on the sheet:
Buttons
Debugging
ESP32
